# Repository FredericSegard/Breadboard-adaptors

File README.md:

# Breadboard-adaptors
 A series of adator PCBs that you can mount chips that are not breadboard friendly, on breadboards.

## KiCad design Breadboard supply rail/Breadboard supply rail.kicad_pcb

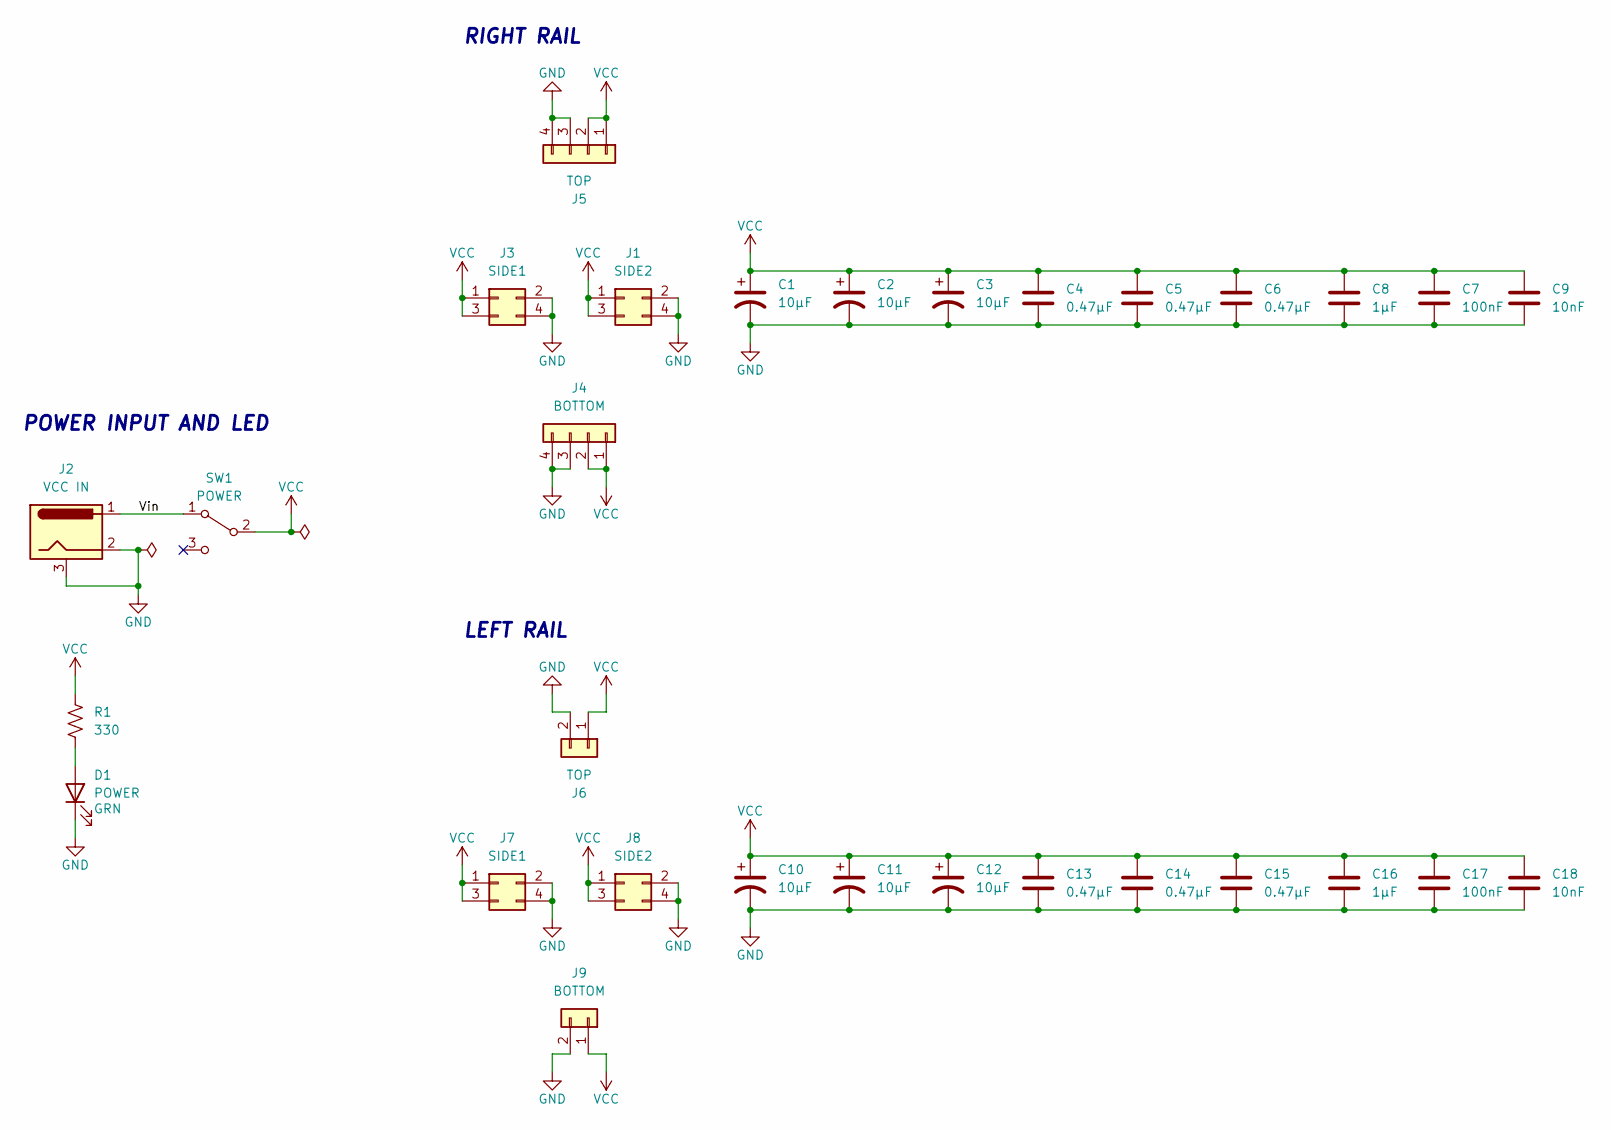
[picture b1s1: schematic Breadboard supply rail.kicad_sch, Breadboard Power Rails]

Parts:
C1, C2, C3, C10, C11, C12: 10µF; CP_Radial_D6.3mm_P2.50mm
C4, C5, C6, C13, C14, C15: 0.47µF; C_Disc_D3.0mm_W2.0mm_P2.50mm
C7, C17: 100nF; C_Disc_D3.0mm_W2.0mm_P2.50mm
C8, C16: 1µF; C_Disc_D3.0mm_W2.0mm_P2.50mm
C9, C18: 10nF; C_Disc_D3.0mm_W2.0mm_P2.50mm
D1: POWER; LED_D5.0mm
J1, J8: SIDE2; PinHeader_2x2_Vertical (Modified)
J2: VCC IN; BarrelJack_Horizontal
J3, J7: SIDE1; PinHeader_2x2_Vertical (Modified)
J4: BOTTOM; PinHeader_1x04_P2.54mm_Horizontal
J5: TOP; PinSocket_1x04_P2.54mm_Horizontal
J6: TOP; PinSocket_1x02_P2.54mm_Horizontal
J9: BOTTOM; PinHeader_1x02_P2.54mm_Horizontal
R1: 330; R_Axial_DIN0207_L6.3mm_D2.5mm_P10.16mm_Horizontal
SW1: POWER; Microswitch_4.7mm_spacing

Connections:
/Vin: J2.1, SW1.1 (A)
GND: C1.2, C2.2, C3.2, C4.2, C5.2, C6.2, C7.2, C8.2, C9.2, C10.2, C11.2, C12.2, C13.2, C14.2, C15.2, C16.2, C17.2, C18.2, D1.1 (K), J1.2, J1.4, J2.2, J2.3, J3.2, J3.4, J4.3, J4.4, J5.3, J5.4, J6.2, J7.2, J7.4, J8.2, J8.4, J9.2
unnamed: D1.2 (A), R1.2
VCC: C1.1, C2.1, C3.1, C4.1, C5.1, C6.1, C7.1, C8.1, C9.1, C10.1, C11.1, C12.1, C13.1, C14.1, C15.1, C16.1, C17.1, C18.1, J1.1, J1.3, J3.1, J3.3, J4.1, J4.2, J5.1, J5.2, J6.1, J7.1, J7.3, J8.1, J8.3, J9.1, R1.1, SW1.2 (B)

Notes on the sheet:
RIGHT RAIL
POWER INPUT AND LED
LEFT RAIL

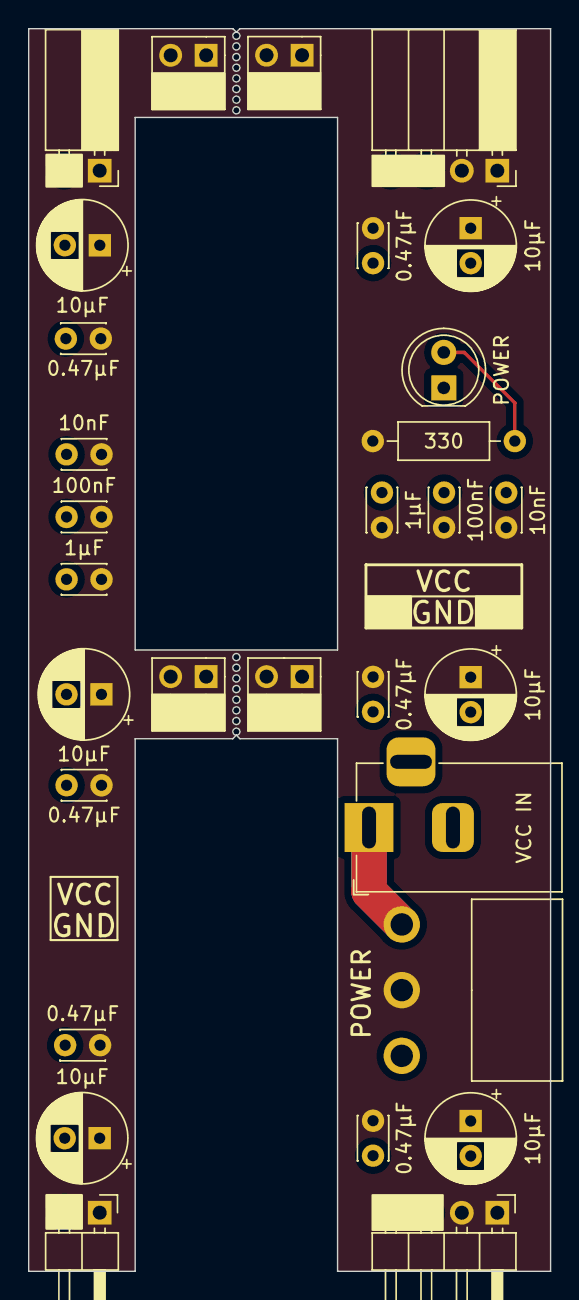
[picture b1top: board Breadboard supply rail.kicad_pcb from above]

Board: 2 copper layers, 37.3 x 88.9 mm, 30 parts (0 on the bottom side), 4 nets.

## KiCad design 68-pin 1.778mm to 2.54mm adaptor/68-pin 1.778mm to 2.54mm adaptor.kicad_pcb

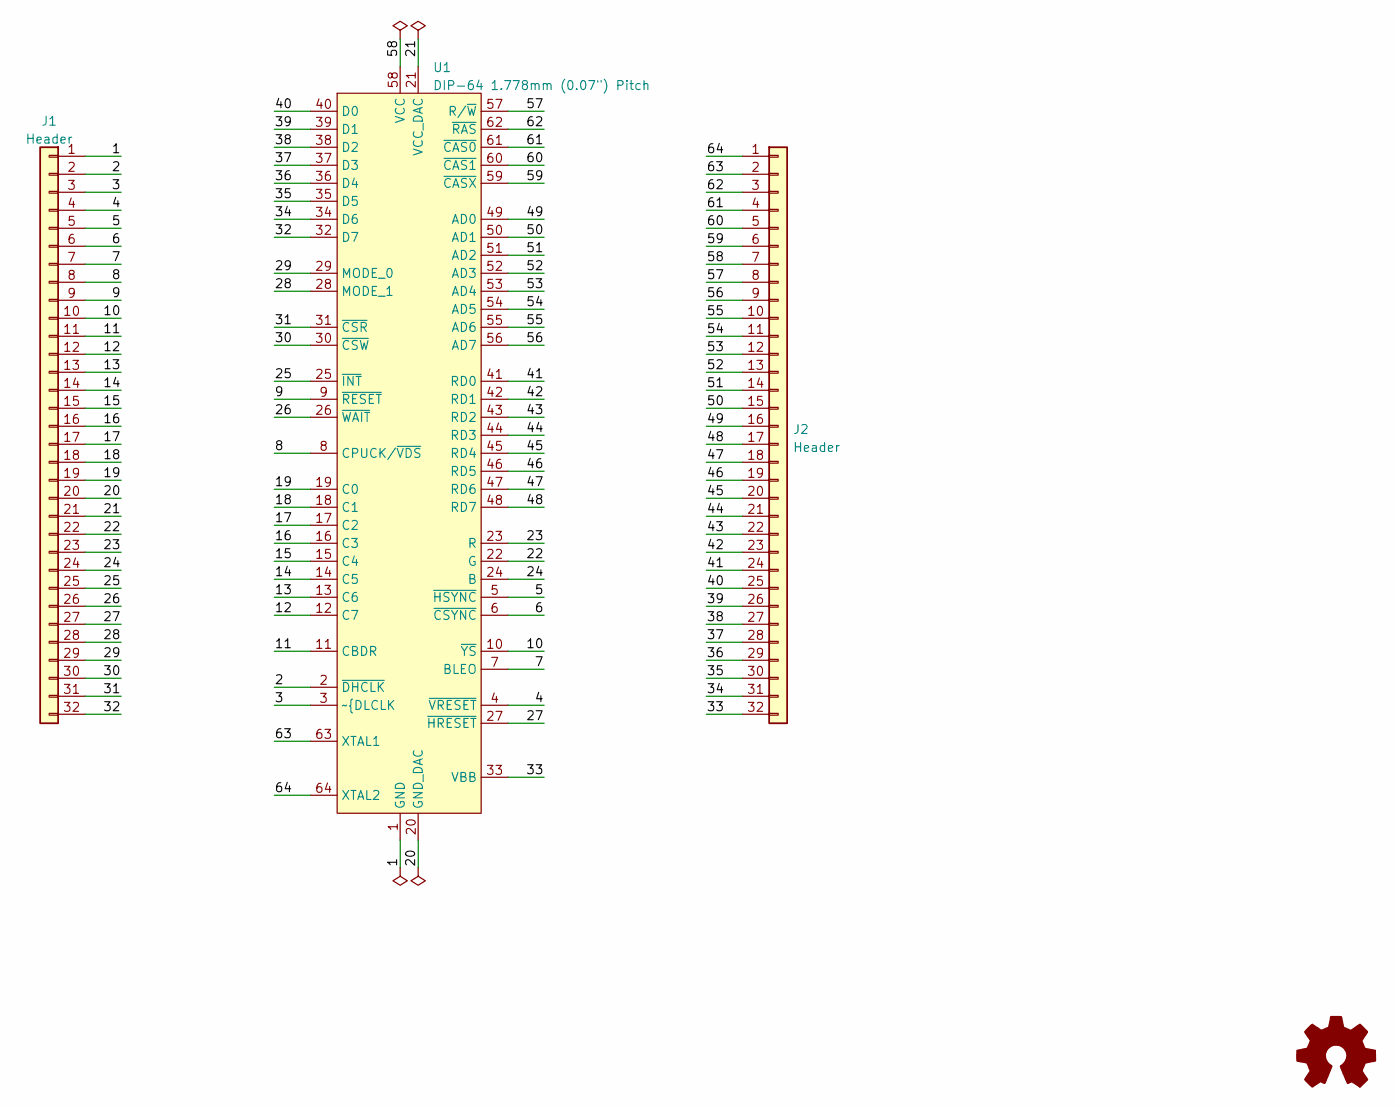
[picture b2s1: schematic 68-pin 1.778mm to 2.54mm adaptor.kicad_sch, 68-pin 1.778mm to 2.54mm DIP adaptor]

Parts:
J1, J2: Header; PinHeader_1x32_P2.54mm_Vertical
U1: DIP-64 1.778mm (0.07") Pitch; DIP 64 1.778 pitch

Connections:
/1: J1.1, U1.1 (GND)
/2: J1.2, U1.2 (~DHCLK)
/3: J1.3, U1.3 (~{DLCLK)
/4: J1.4, U1.4 (~VRESET)
/5: J1.5, U1.5 (~HSYNC)
/6: J1.6, U1.6 (~CSYNC)
/7: J1.7, U1.7 (BLEO)
/8: J1.8, U1.8 (CPUCK/~VDS)
/9: J1.9, U1.9 (~RESET)
/10: J1.10, U1.10 (~YS)
/11: J1.11, U1.11 (CBDR)
/12: J1.12, U1.12 (C7)
/13: J1.13, U1.13 (C6)
/14: J1.14, U1.14 (C5)
/15: J1.15, U1.15 (C4)
/16: J1.16, U1.16 (C3)
/17: J1.17, U1.17 (C2)
/18: J1.18, U1.18 (C1)
/19: J1.19, U1.19 (C0)
/20: J1.20, U1.20 (GND_DAC)
/21: J1.21, U1.21 (VCC_DAC)
/22: J1.22, U1.22 (G)
/23: J1.23, U1.23 (R)
/24: J1.24, U1.24 (B)
/25: J1.25, U1.25 (~INT)
/26: J1.26, U1.26 (~WAIT)
/27: J1.27, U1.27 (~HRESET)
/28: J1.28, U1.28 (MODE_1)
/29: J1.29, U1.29 (MODE_0)
/30: J1.30, U1.30 (~CSW)
/31: J1.31, U1.31 (~CSR)
/32: J1.32, U1.32 (D7)
/33: J2.32, U1.33 (VBB)
/34: J2.31, U1.34 (D6)
/35: J2.30, U1.35 (D5)
/36: J2.29, U1.36 (D4)
/37: J2.28, U1.37 (D3)
/38: J2.27, U1.38 (D2)
/39: J2.26, U1.39 (D1)
/40: J2.25, U1.40 (D0)
/41: J2.24, U1.41 (RD0)
/42: J2.23, U1.42 (RD1)
/43: J2.22, U1.43 (RD2)
/44: J2.21, U1.44 (RD3)
/45: J2.20, U1.45 (RD4)
/46: J2.19, U1.46 (RD5)
/47: J2.18, U1.47 (RD6)
/48: J2.17, U1.48 (RD7)
/49: J2.16, U1.49 (AD0)
/50: J2.15, U1.50 (AD1)
/51: J2.14, U1.51 (AD2)
/52: J2.13, U1.52 (AD3)
/53: J2.12, U1.53 (AD4)
/54: J2.11, U1.54 (AD5)
/55: J2.10, U1.55 (AD6)
/56: J2.9, U1.56 (AD7)
/57: J2.8, U1.57 (R/~W)
/58: J2.7, U1.58 (VCC)
/59: J2.6, U1.59 (~CASX)
/60: J2.5, U1.60 (~CAS1)
/61: J2.4, U1.61 (~CAS0)
/62: J2.3, U1.62 (~RAS)
/63: J2.2, U1.63 (XTAL1)
/64: J2.1, U1.64 (XTAL2)

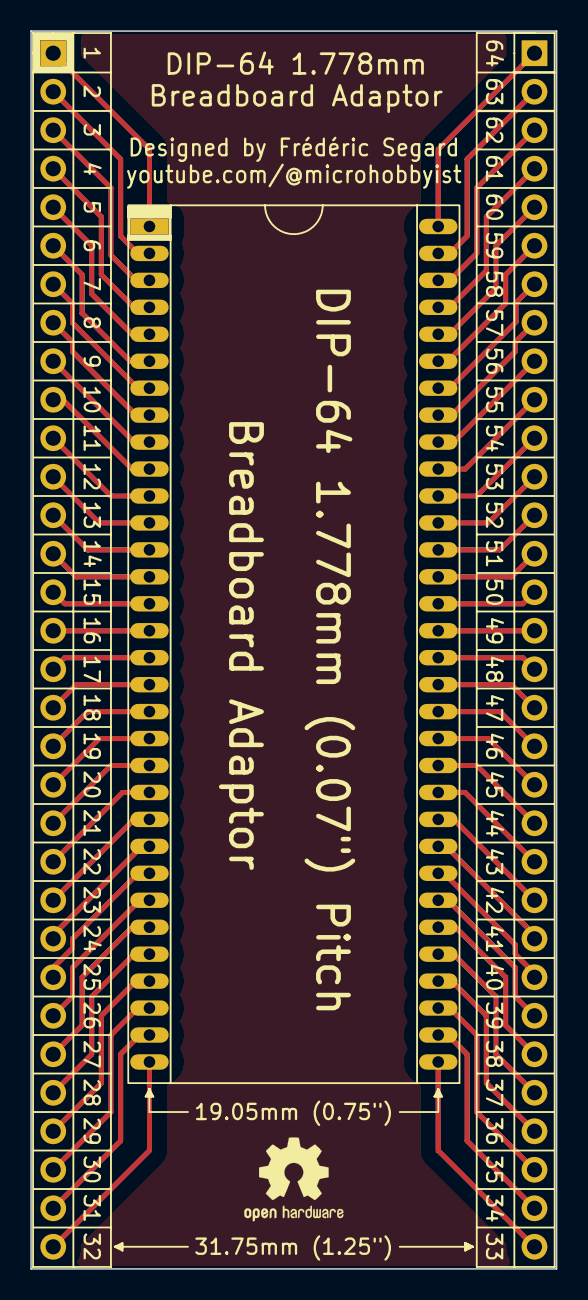
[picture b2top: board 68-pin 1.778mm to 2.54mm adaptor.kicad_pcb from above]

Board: 2 copper layers, 34.7 x 81.7 mm, 4 parts (0 on the bottom side), 64 nets.

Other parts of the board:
REF1: OSHW-Logo2_7.3x6mm_SilkScreen

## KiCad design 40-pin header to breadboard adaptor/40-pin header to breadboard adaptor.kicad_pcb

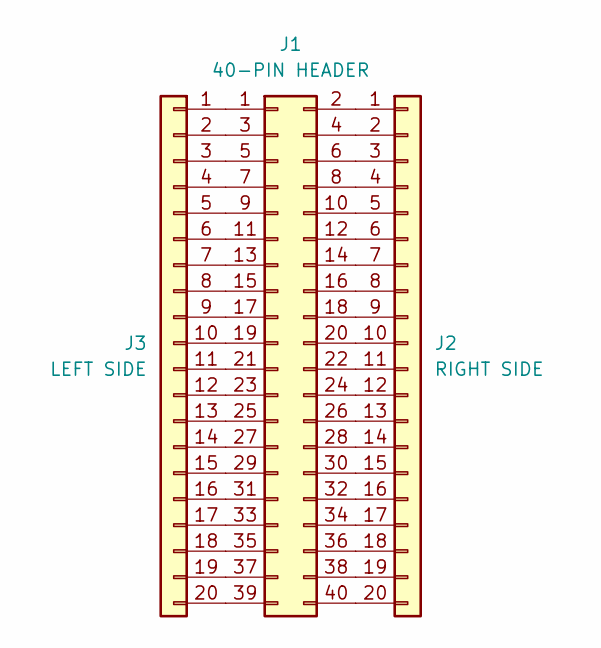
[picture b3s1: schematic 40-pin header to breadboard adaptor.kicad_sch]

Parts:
J1: 40-PIN HEADER; PinHeader_2x20_P2.54mm_Vertical
J2: RIGHT SIDE; PinHeader_1x20_P2.54mm_Vertical
J3: LEFT SIDE; PinHeader_1x20_P2.54mm_Vertical

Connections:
unnamed: J1.1, J3.1
unnamed: J1.2, J2.1
unnamed: J1.3, J3.2
unnamed: J1.4, J2.2
unnamed: J1.5, J3.3
unnamed: J1.6, J2.3
unnamed: J1.7, J3.4
unnamed: J1.8, J2.4
unnamed: J1.9, J3.5
unnamed: J1.10, J2.5
unnamed: J1.11, J3.6
unnamed: J1.12, J2.6
unnamed: J1.13, J3.7
unnamed: J1.14, J2.7
unnamed: J1.15, J3.8
unnamed: J1.16, J2.8
unnamed: J1.17, J3.9
unnamed: J1.18, J2.9
unnamed: J1.19, J3.10
unnamed: J1.20, J2.10
unnamed: J1.21, J3.11
unnamed: J1.22, J2.11
unnamed: J1.23, J3.12
unnamed: J1.24, J2.12
unnamed: J1.25, J3.13
unnamed: J1.26, J2.13
unnamed: J1.27, J3.14
unnamed: J1.28, J2.14
unnamed: J1.29, J3.15
unnamed: J1.30, J2.15
unnamed: J1.31, J3.16
unnamed: J1.32, J2.16
unnamed: J1.33, J3.17
unnamed: J1.34, J2.17
unnamed: J1.35, J3.18
unnamed: J1.36, J2.18
unnamed: J1.37, J3.19
unnamed: J1.38, J2.19
unnamed: J1.39, J3.20
unnamed: J1.40, J2.20

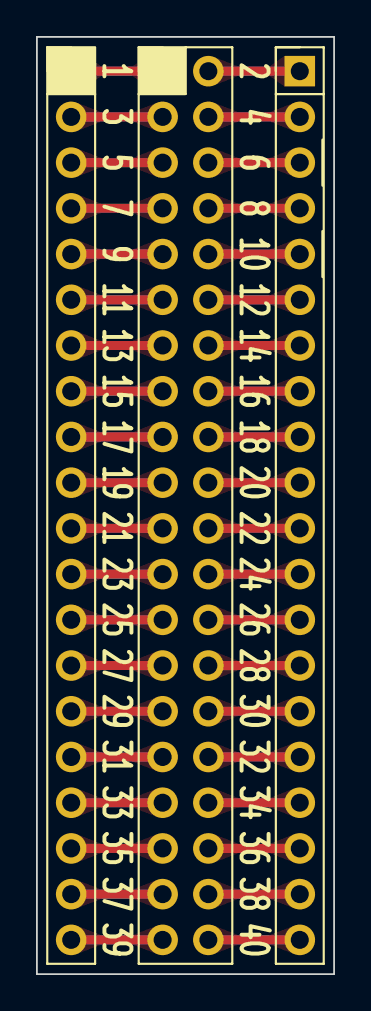
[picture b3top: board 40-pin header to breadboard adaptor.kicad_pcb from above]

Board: 2 copper layers, 16.5 x 52.1 mm, 3 parts (0 on the bottom side), 40 nets.

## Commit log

2023-08-25 Adding the complete project
2023-08-26 Adding a 1.778mm DIP adaptor
2023-09-11 Added a Power Rail distribution panelized PCB for breadboards
2023-09-24 Backups, please ignore
